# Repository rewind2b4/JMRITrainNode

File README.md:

# JMRITrainNode
TrainNode is a JMRI compatible I/O controller built on the MQTT protocol. Using the Raspberry Pi Pico, each node can support up to 16 turnouts as standard, or more with user addons.

## Installation
- To use TrainNode, you must have a MQTT server with username and password authentication connected to JMRI ([JMRI + MQTT](https://www.jmri.org/help/en/html/hardware/mqtt/index.shtml)), additionally you must have access to WIFI in close proximity to your layout for optimal performance. It is recommended to use Eclipse Mosquitto as your MQTT broker.
- To install TrainNode on the Rpi Pico W, install MicroPython for Pico-W ([MicroPython](https://micropython.org/download/RPI_PICO_W/)).
- Next, configure the TrainNode [config.py](https://github.com/rewind2b4/JMRITrainNode/tree/master/Code/config.py) file (see Docs for more info). 
- Finally, copy the 4 files from the [code](https://github.com/rewind2b4/JMRITrainNode/tree/master/Code) folder to the Pico.
- The Pico-W will automatically connect to the internet through the installation WIFI connection, download the required dependencies, and then restart, connecting to the layout MQTT broker through the layout WIFI connection (for layout networks that are disconnected from internet).

## Docs
Network / MQTT Settings
- Ssid (The WIFI connection used to access the MQTT server)
- Password (The WIFI connection used to access the MQTT server)
- Installation_Ssid (The WIFI connection used to access the internet for autoconfig)
- Installation_Password (The WIFI connection used to access the internet for autoconfig)
- Server_addr (The MQTT server address)
- Client_name (The MQTT client name)
- MQTT_User (The username to the MQTT server)
- MQTT_Password (The password to the MQTT server)
- MQTT_Port (Usually 1883)
- MQTT_Prefix (The base topic that all JMRI topics are based on, defined in JMRI MQTT config)

Device Settings
- Ramp_Rate (PWM Ramp delay per step in seconds)
- PWM_Freq (PWM Frequency in Hz)
- Debounce_delay (Switch debounce delay in seconds)
- Neopixel_pin (The pin used to shift out bits to any neopixels) (None if not used)

Server Configuration Settings
- The topics used by JMRI to publish certain events to 
- turnout_HIGH = "THROWN"
- turnout_LOW = "CLOSED"
- light_HIGH = "ON"
- light_LOW = "OFF"
- sensor_HIGH = "ACTIVE"
- sensor_LOW = "INACTIVE"

MQTT_Addresses
- Devices to be controlled by TrainNode
- The number of devices is not limited except by the program execution time and physical I/O limitations of the Pico-W
- Available Device Types
   - Servo [PWM Pin(int), Min PWM(int), Max PWM(int), Ramp Enable(bool)] (OUTPUT)
   - Neopixel [Neopixel Index(int), Color ON([int, int, int], Color OFF[int, int, int]] (OUTPUT)
   - LED [LED Pin(int)] (OUTPUT)
   - Pin [Pin(int)] (OUTPUT)
   - General_OUT [] (OUTPUT)
   - Button_Latching [Button Pin(int), Pin State High(bool)] (INPUT)
   - Pin_Scan [Pin(int), Pin State High(bool)] (INPUT)
   - General_IN [] (INPUT)

## Upcoming Features
- Webserver for changing configuration
- Service that detects TrainNodes and allows for easy management (similar in functionality to a service such as QNAP finder)
- The ability to address multiple Neopixel buses
- Code optimisation
- Add photos to repo
- Removal of MIP install service

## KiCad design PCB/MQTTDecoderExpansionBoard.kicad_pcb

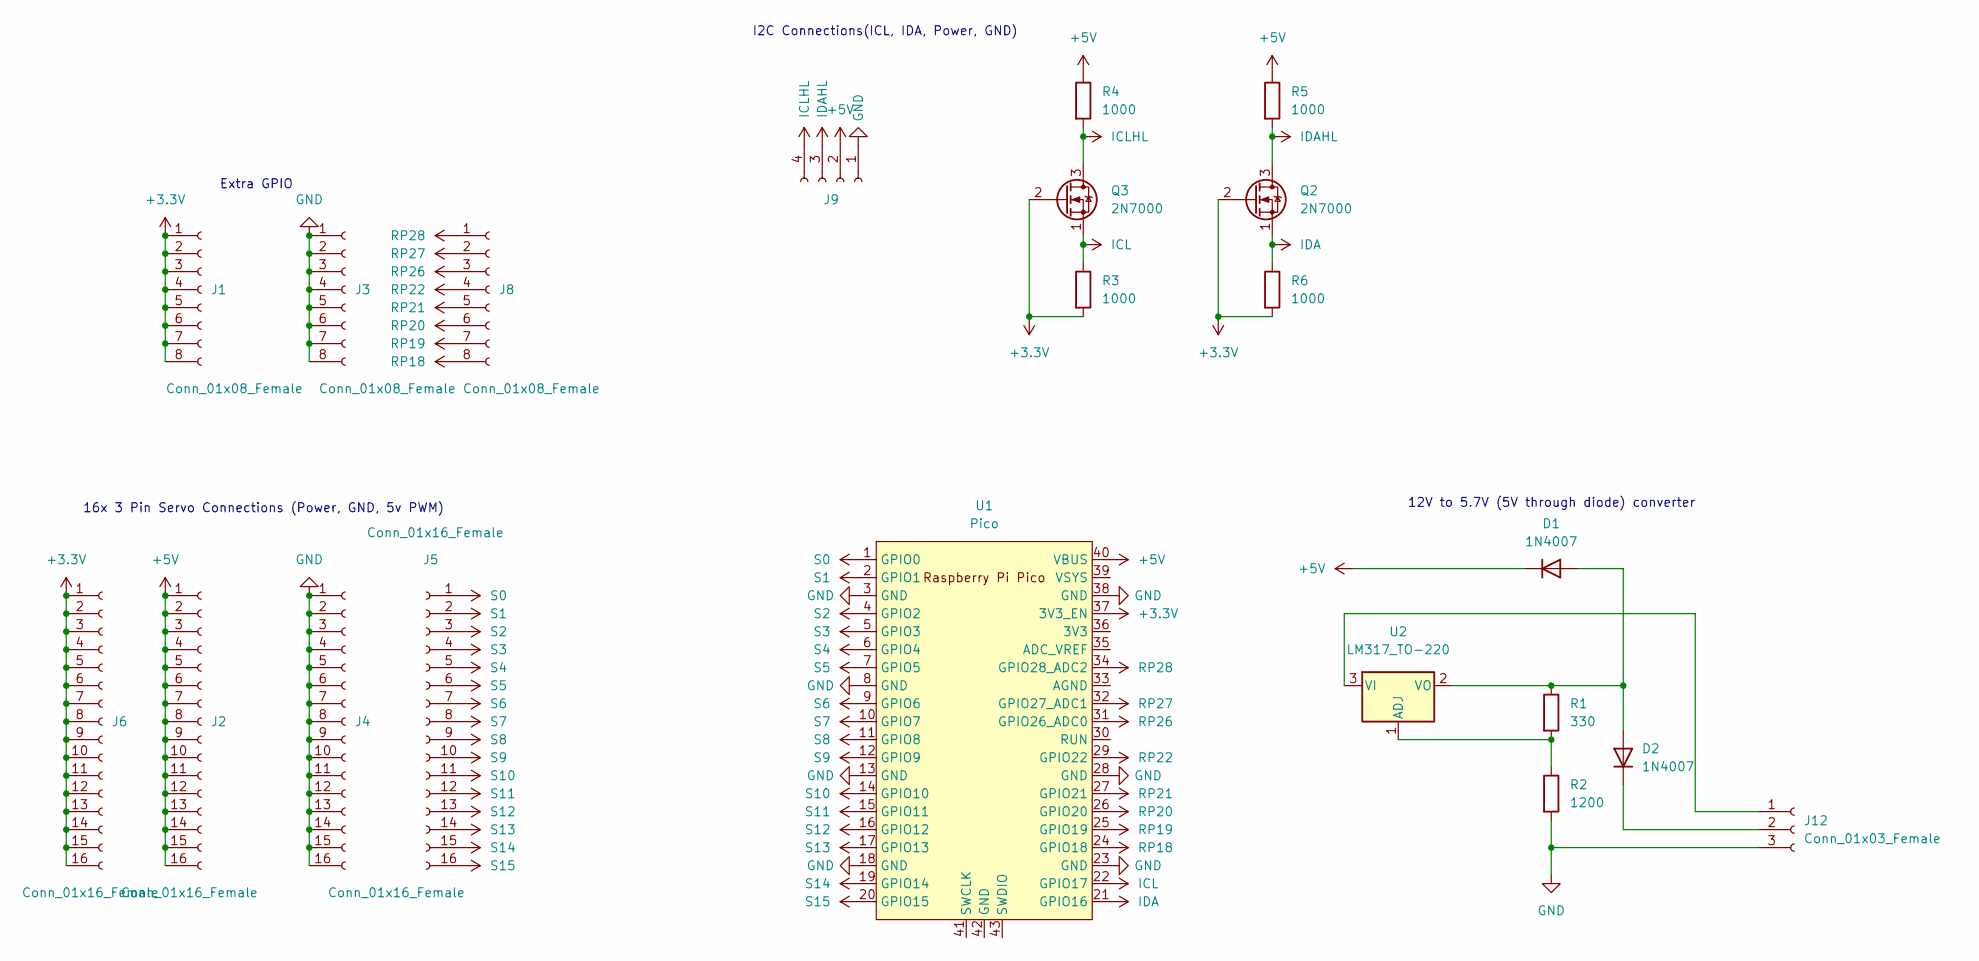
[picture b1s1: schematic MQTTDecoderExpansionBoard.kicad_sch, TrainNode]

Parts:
D1, D2: 1N4007; D_0603_1608Metric
J1, J3, J8: Conn_01x08_Female; PinHeader_1x08_P2.54mm_Vertical
J2, J4, J5, J6: Conn_01x16_Female; PinHeader_1x16_P2.54mm_Vertical
J9: Conn_01x04_Socket; JST_SH_SM04B-SRSS-TB_1x04-1MP_P1.00mm_Horizontal
J12: Conn_01x03_Female; TerminalBlock_Altech_AK300-3_P5.00mm
Q2, Q3: 2N7000; TO-92_Inline
R1: 330; R_0603_1608Metric
R2: 1200; R_0603_1608Metric
R3, R4, R5, R6: 1000; R_0603_1608Metric
U1: Pico; RPi_Pico_SMD_TH
U2: LM317_TO-220; TO-220-3_Vertical

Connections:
+3.3V: J1.1, J1.2, J1.3, J1.4, J1.5, J1.6, J1.7, J1.8, J6.1, J6.2, J6.3, J6.4, J6.5, J6.6, J6.7, J6.8, J6.9, J6.10, J6.11, J6.12, J6.13, J6.14, J6.15, J6.16, Q2.2 (G), Q3.2 (G), R3.2, R6.2, U1.37 (3V3_EN)
+5V: D1.1 (K), J2.1, J2.2, J2.3, J2.4, J2.5, J2.6, J2.7, J2.8, J2.9, J2.10, J2.11, J2.12, J2.13, J2.14, J2.15, J2.16, J9.2, R4.1, R5.1, U1.40 (VBUS)
GND: J3.1, J3.2, J3.3, J3.4, J3.5, J3.6, J3.7, J3.8, J4.1, J4.2, J4.3, J4.4, J4.5, J4.6, J4.7, J4.8, J4.9, J4.10, J4.11, J4.12, J4.13, J4.14, J4.15, J4.16, J9.1, J12.3, R2.2, U1.3 (GND), U1.8 (GND), U1.13 (GND), U1.18 (GND), U1.23 (GND), U1.28 (GND), U1.38 (GND)
ICL: Q3.1 (S), R3.1, U1.22 (GPIO17)
ICLHL: J9.4, Q3.3 (D), R4.2
IDA: Q2.1 (S), R6.1, U1.21 (GPIO16)
IDAHL: J9.3, Q2.3 (D), R5.2
unnamed: D1.2 (A), D2.2 (A), R1.1, U2.2 (VO)
unnamed: D2.1 (K), J12.2
unnamed: J12.1, U2.3 (VI)
unnamed: R1.2, R2.1, U2.1 (ADJ)
RP18: J8.8, U1.24 (GPIO18)
RP19: J8.7, U1.25 (GPIO19)
RP20: J8.6, U1.26 (GPIO20)
RP21: J8.5, U1.27 (GPIO21)
RP22: J8.4, U1.29 (GPIO22)
RP26: J8.3, U1.31 (GPIO26_ADC0)
RP27: J8.2, U1.32 (GPIO27_ADC1)
RP28: J8.1, U1.34 (GPIO28_ADC2)
S0: J5.1, U1.1 (GPIO0)
S1: J5.2, U1.2 (GPIO1)
S2: J5.3, U1.4 (GPIO2)
S3: J5.4, U1.5 (GPIO3)
S4: J5.5, U1.6 (GPIO4)
S5: J5.6, U1.7 (GPIO5)
S6: J5.7, U1.9 (GPIO6)
S7: J5.8, U1.10 (GPIO7)
S8: J5.9, U1.11 (GPIO8)
S9: J5.10, U1.12 (GPIO9)
S10: J5.11, U1.14 (GPIO10)
S11: J5.12, U1.15 (GPIO11)
S12: J5.13, U1.16 (GPIO12)
S13: J5.14, U1.17 (GPIO13)
S14: J5.15, U1.19 (GPIO14)
S15: J5.16, U1.20 (GPIO15)

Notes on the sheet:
Extra GPIO
I2C Connections(ICL, IDA, Power, GND)
12V to 5.7V (5V through diode) converter
16x 3 Pin Servo Connections (Power, GND, 5v PWM)

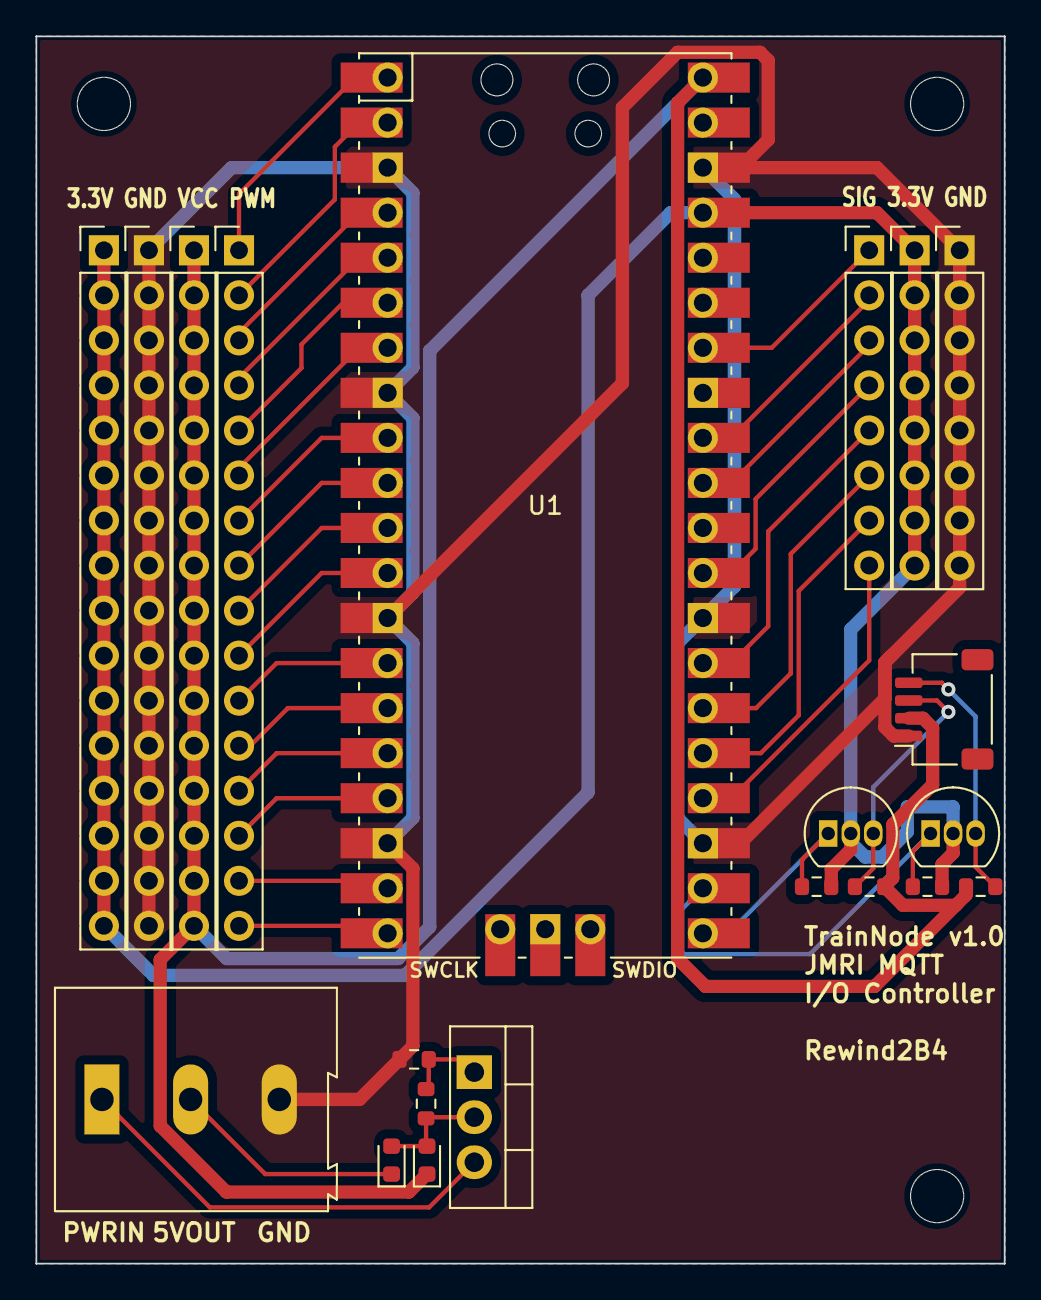
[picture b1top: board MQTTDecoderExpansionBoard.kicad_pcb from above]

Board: 2 copper layers, 54.6 x 69.2 mm, 21 parts (0 on the bottom side), 35 nets.

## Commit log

2024-08-16 added files for v0.01 release
2024-08-17 fixed up files
2024-08-17 Rename cern_ohl_w_v2.txt to LICENSE
2024-08-21 version 0.1 pcb
2024-12-01 Added NFC reporter
2024-12-12 testing webserver
2024-12-22 tested json. going to implement into main
2024-12-22 started rebuilding main
2024-12-23 added servo call structure
2024-12-23 started working on changing settings over mqtt
2024-12-23 added more io functions
2024-12-23 organising repo
2024-12-30 30.12.2024
2024-12-30 removed pc run
2025-04-20 fixed button latch and pin in
2025-04-20 worked on rfid
2025-04-23 neatened code
2025-04-23 added neopixel control
2025-04-24 add timeout function, tested multi rfid readers
2025-04-24 wlan change. not sure about this yet
